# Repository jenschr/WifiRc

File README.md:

# Wifi RC project
A simple board to make RC projects from. Has three simple motor controllers, 6 prewired LED connections, SPI and Serial outputs & more.

Can run off USB (no motor) or 7.4 or 11.1V batteries (depending on what your motors need). Set your power source using the VS jumper. The 5V outputs are intended to dirve Servo's, but the wiring isn't exactly ideal. A new version may set aside 3 pins for dedicated Servo outputs.

The module has been produced and tested, but not yet mounted in a model. See pictures of the reflowed and soldered board [here](http://jcprojects.tumblr.com/post/149121660034/my-second-dev-board-based-on-the-particleio-p1) and a short video from testing [here](http://jcprojects.tumblr.com/post/154342641139/so-much-blink-all-pins-mapped-out-and-tested-i).

## BOM
The [bill of materials](/Dumper001/Dumper001.csv) can be found as a .csv file in this repository. The core part is the P1 module (USI WM-N-BM-14) that you can pick up in a [10-pack from the Particle store](https://store.particle.io/products/p1), pre-flashed with the Particle firmware ([P1 datasheet/docs](https://docs.particle.io/datasheets/p1-datasheet/)).

I have used AMS1117 for both 3.3 and 5V regulation and that seems to work well without any signs of overheating. The L9110 motor drivers are weak, but will do the trick for small motors.

## Errata
* The pin marked D6 is UART2_CTS,(pin 30) accessable as WKP.
* The pin marked as SS is DAC (pin 24). A2 is the actual SS pin for SPI1.

Both of these pins work for digital IO, but use the constant WKP to access the D6 pin and DAC to access the pin marked SS.

## License
[CERN OHL V1.2](http://www.ohwr.org/licenses/cern-ohl/v1.2)

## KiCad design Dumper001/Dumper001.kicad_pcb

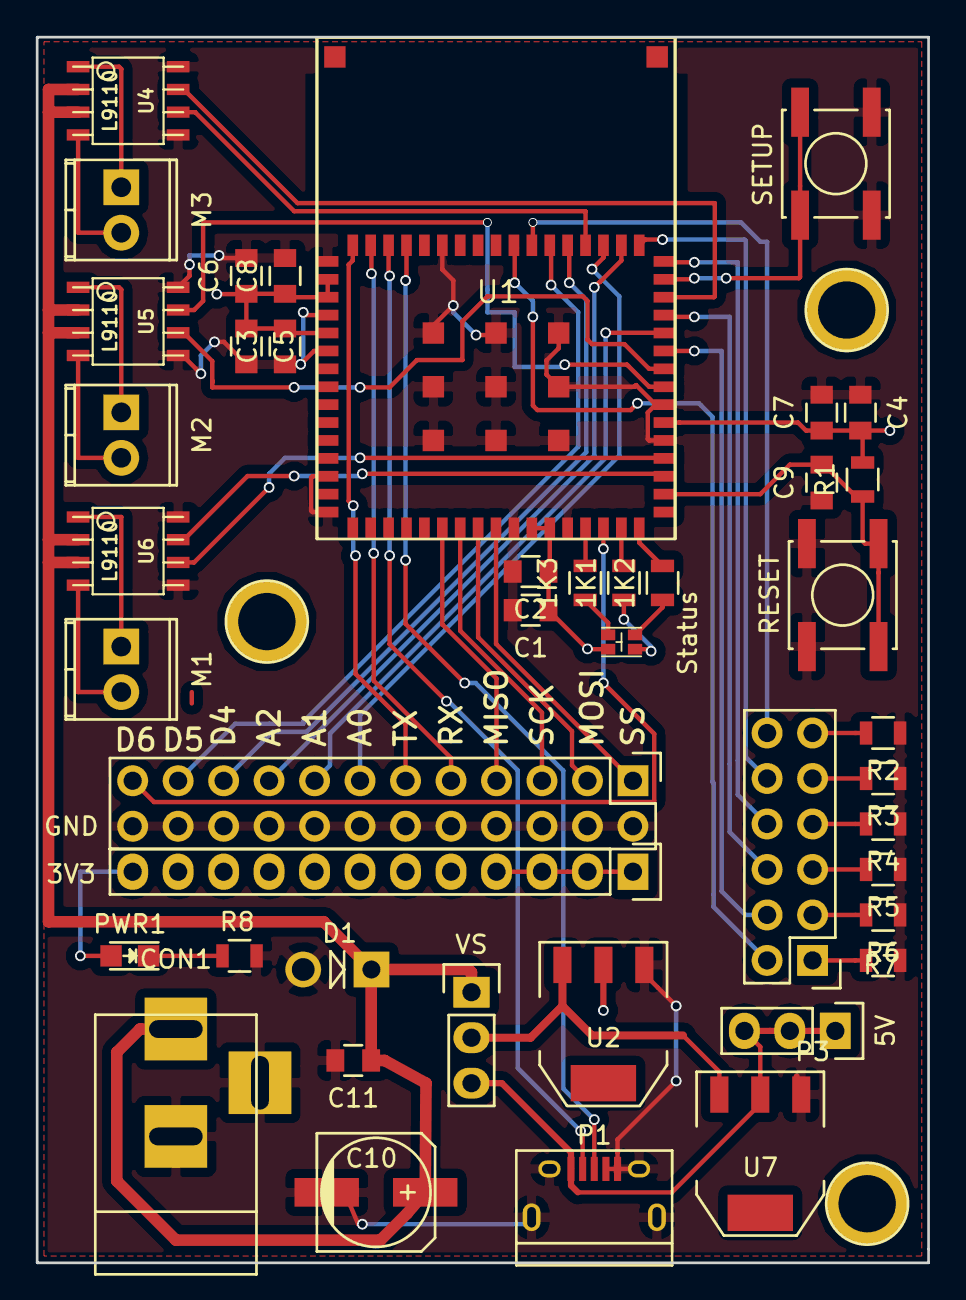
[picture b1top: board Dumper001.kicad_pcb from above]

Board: 2 copper layers, 49.8 x 68.5 mm, 43 parts (0 on the bottom side), 52 nets.

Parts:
1K1, 1K2, 1K3: 1k; R_0805
3V3: CONN_01X12; Pin_Header_Straight_1x12
5V: CONN_01X03; Pin_Header_Straight_1x03
C1, C3, C6, C7, C9, C11: 0.1uf; C_0805
C2, C4, C5, C8: 10uf; C_0805
C10: 47uf; c_elec_6.3x5.7
CON1: BARREL_JACK
D1: InDiode; Diode_DO-41_SOD81_Vertical_AnodeUp
GND: CONN_02X12; Pin_Header_Straight_2x12
M1: M1; TerminalBlock_Pheonix_MPT-2.54mm_2pol
M2: M2; TerminalBlock_Pheonix_MPT-2.54mm_2pol
M3: M3; TerminalBlock_Pheonix_MPT-2.54mm_2pol
P1: USB_OTG; USB_Micro-B
P3: LedConnector; Pin_Header_Straight_2x06
PWR1: LED; LED_0805
R1: 10k; R_0805
R2, R3, R4, R5, R6, R7: 470R; R_0805
R8: 1000R; R_0805
RESET: SW_PUSH; SW_SPST_EVPBF
SETUP: SW_PUSH; SW_SPST_EVPBF
Status: RGB_LED; 0605_RGB_LED
U1: WM-N-BM-14
U2: AMS1117 3.3V; SOT-223
U4, U5, U6: L9110; so-8
U7: AMS1117 5.0V; SOT-223
VS: CONN_01X03; Pin_Header_Straight_1x03

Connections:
+3V3: 3V3.1, 3V3.2, 3V3.3, 3V3.4, 3V3.5, 3V3.6, 3V3.7, 3V3.8, 3V3.9, 3V3.10, 3V3.11, 3V3.12, C1.1, C2.1, C3.2, C4.2, C5.1, C6.1, C7.1, C8.1, PWR1.2, R1.2, Status.1, U1.2, U1.3, U1.5, U1.26, U1.27, U1.38, U2.2
+5V: 5V.1, 5V.2, 5V.3, P1.1, U7.2, VS.3
+12V: C10.1, C11.1, CON1.1, D1.1, U4.2, U4.3, U5.2, U5.3, U6.2, U6.3, VS.1
GND: C1.2, C2.2, C3.1, C4.1, C5.2, C6.2, C7.2, C8.2, C9.1, C10.2, C11.2, CON1.2, CON1.3, D1.2, GND.2, GND.4, GND.6, GND.8, GND.10, GND.12, GND.14, GND.16, GND.18, GND.20, GND.22, GND.24, P1.4, P1.5, P1.6, R2.1, R3.1, R4.1, R5.1, R6.1, R7.1, R8.1, RESET.1, SETUP.1, U1.1, U1.4, U1.6, U1.13, U1.15, U1.25, U1.28, U1.37, U1.39, U1.59, U1.65, U1.66, U1.67, U1.68, U1.69, U1.70, U1.71, U1.72, U1.73, U2.1, U4.5, U4.8, U5.5, U5.8, U6.5, U6.8, U7.1
GPIO_A0: GND.13, U1.50
GPIO_A1: GND.15, U1.43
GPIO_A2: GND.17, U1.49
GPIO_D4: GND.19, U1.52
GPIO_D5: GND.21, U1.53
GPIO_D6: GND.23, U1.30
LED1: P3.2, U1.55
LED2: P3.4, U1.42
LED3: P3.6, U1.44
LED4: P3.8, U1.47
LED5: P3.10, U1.48
LED6: P3.12, U1.54
M1a: M1.1, U6.1
M1b: M1.2, U6.4
M2a: M2.1, U5.1
M2b: M2.2, U5.4
M3a: M3.1, U4.1
M3b: M3.2, U4.4
MISO: GND.7, U1.21
MOSI: GND.3, U1.23
unnamed: 1K1.1, Status.4
unnamed: 1K1.2, U1.31
unnamed: 1K2.1, Status.3
unnamed: 1K2.2, U1.32
unnamed: 1K3.1, Status.2
unnamed: 1K3.2, U1.29
unnamed: P3.1, R7.2
unnamed: P3.3, R6.2
unnamed: P3.5, R5.2
unnamed: P3.7, R4.2
unnamed: P3.9, R3.2
unnamed: P3.11, R2.2
unnamed: U2.3, U7.3, VS.2
unnamed: PWR1.1, R8.2
unnamed: U1.35, U6.7
unnamed: U1.36, U6.6
unnamed: U1.40, U5.7
unnamed: U1.41, U5.6
unnamed: U1.45, U4.7
unnamed: U1.51, U4.6
RESET: C9.2, R1.1, RESET.2, U1.34
RX: GND.9, U1.63
SCK: GND.5, U1.22
SETUP: SETUP.2, U1.46
SS: GND.1, U1.24
TX: GND.11, U1.64
USBD+: P1.3, U1.61
USBD-: P1.2, U1.62

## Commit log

2016-12-11 first
2016-12-11 adding image
2016-12-11 adding bom link
2016-12-11 adding another image to doc
2016-12-11 text tweak
2016-12-11 docs link
2018-07-10 Aligned Readme.md file Text Head Syntax
